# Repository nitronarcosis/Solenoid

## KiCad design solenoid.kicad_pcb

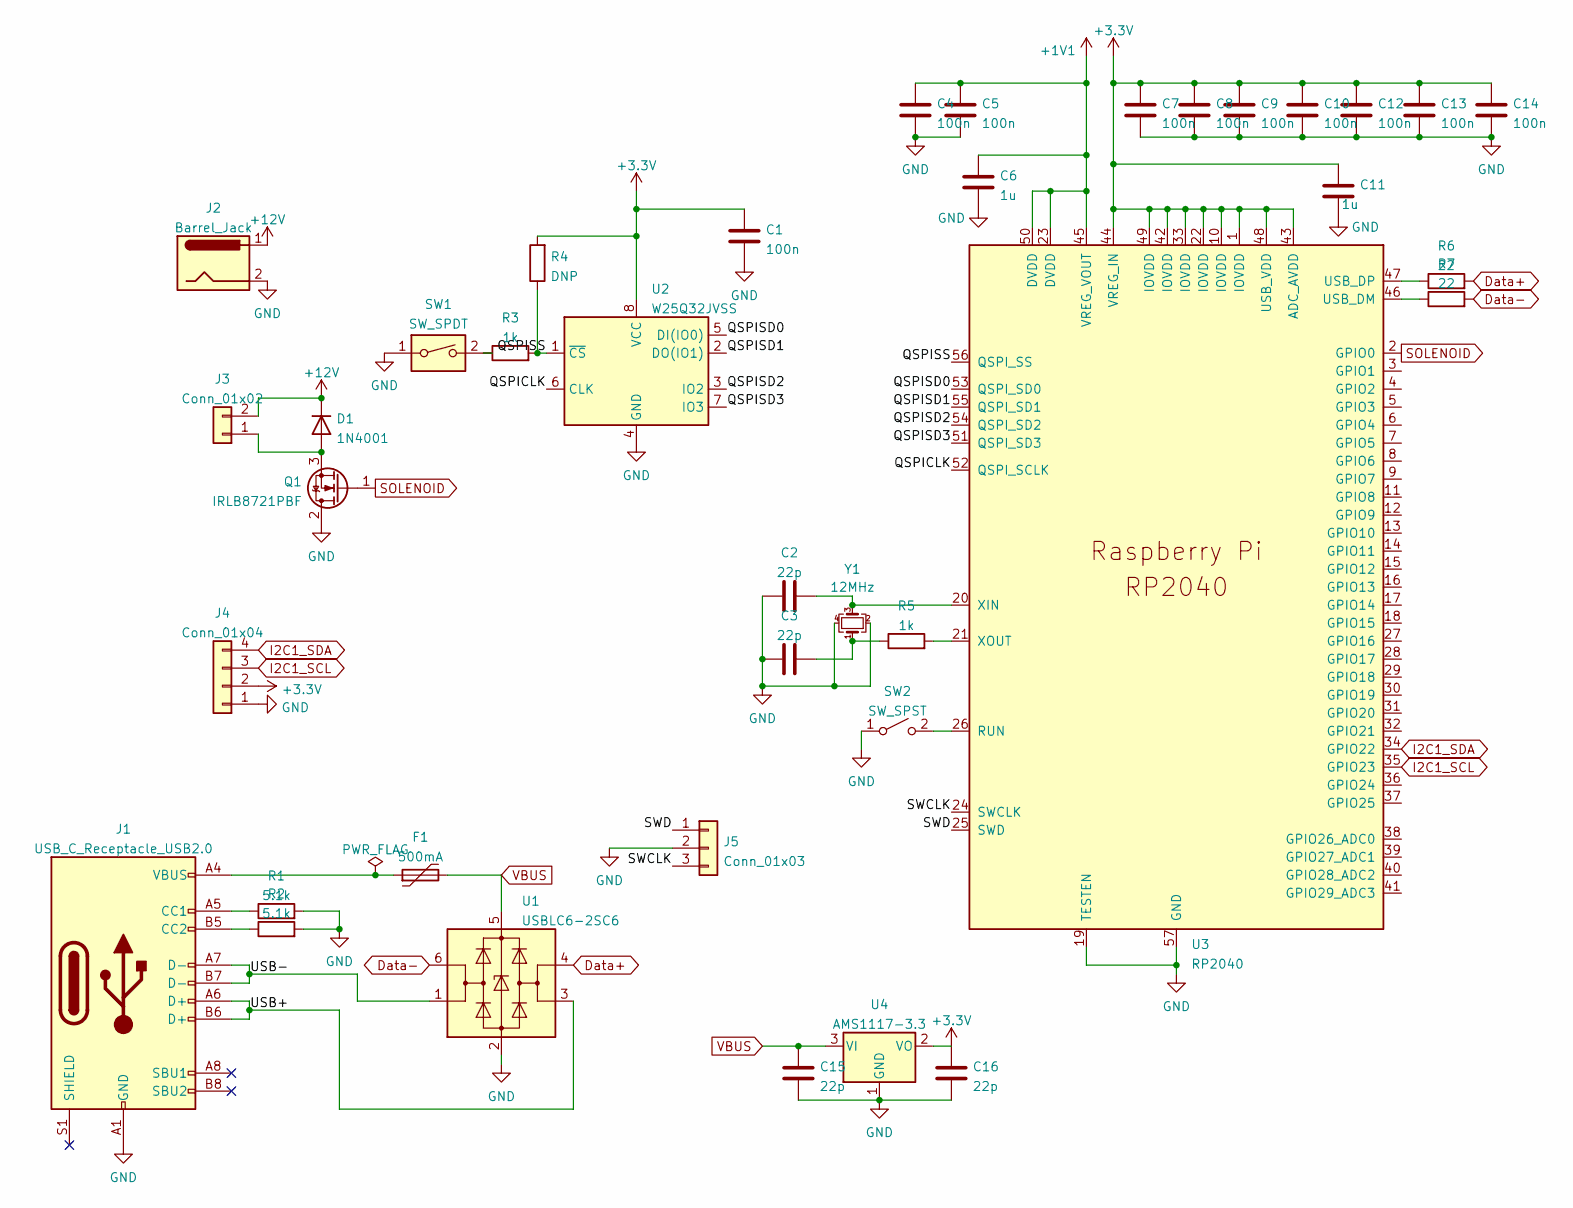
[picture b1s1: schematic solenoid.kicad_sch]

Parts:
C1, C4, C5, C7, C8, C9, C10, C12, C13, C14: 100n; C_0603_1608Metric
C2, C3, C15, C16: 22p; C_0603_1608Metric
C6, C11: 1u; C_0603_1608Metric
D1: 1N4001; D_DO-41_SOD81_P10.16mm_Horizontal
F1: 500mA; Fuse_1206_3216Metric_Pad1.42x1.75mm_HandSolder
J1: USB_C_Receptacle_USB2.0; USB_C_Receptacle_HRO_TYPE-C-31-M-12
J2: Barrel_Jack; BarrelJack_CUI_PJ-063AH_Horizontal
J3: Conn_01x02; PinHeader_1x02_P2.54mm_Vertical
J4: Conn_01x04; PinHeader_1x04_P2.54mm_Vertical
J5: Conn_01x03; PinHeader_1x03_P2.54mm_Vertical
Q1: IRLB8721PBF; TO-220-3_Vertical
R1, R2: 5.1k; R_0603_1608Metric
R3, R5: 1k; R_0603_1608Metric
R4: DNP; R_0603_1608Metric
R6, R7: 22; R_0603_1608Metric
SW1: SW_SPDT; SW_DIP_SPSTx01_Slide_Omron_A6S-110x_W8.9mm_P2.54mm
SW2: SW_SPST; SW_SPST_EVQP0
U1: USBLC6-2SC6; SOT-23-6
U2: W25Q32JVSS; SOIC-8_5.23x5.23mm_P1.27mm
U3: RP2040; RP2040-QFN-56
U4: AMS1117-3.3; SOT-223-3_TabPin2
Y1: 12MHz; Crystal_SMD_3225-4Pin_3.2x2.5mm

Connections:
+1V1: C4.1, C5.1, C6.1, U3.23 (DVDD), U3.45 (VREG_VOUT), U3.50 (DVDD)
+3V3: C1.1, C7.1, C8.1, C9.1, C10.1, C11.1, C12.1, C13.1, C14.1, C16.2, J4.2, R4.2, U2.8 (VCC), U3.1 (IOVDD), U3.10 (IOVDD), U3.22 (IOVDD), U3.33 (IOVDD), U3.42 (IOVDD), U3.43 (ADC_AVDD), U3.44 (VREG_IN), U3.48 (USB_VDD), U3.49 (IOVDD), U4.2 (VO)
+12V: D1.1 (K), J2.1, J3.2
/QSPICLK: U2.6 (CLK), U3.52 (QSPI_SCLK)
/QSPISD0: U2.5 (DI(IO0)), U3.53 (QSPI_SD0)
/QSPISD1: U2.2 (DO(IO1)), U3.55 (QSPI_SD1)
/QSPISD2: U2.3 (IO2), U3.54 (QSPI_SD2)
/QSPISD3: U2.7 (IO3), U3.51 (QSPI_SD3)
/QSPISS: R3.2, R4.1, U2.1 (~CS), U3.56 (QSPI_SS)
/SWCLK: J5.3, U3.24 (SWCLK)
/SWD: J5.1, U3.25 (SWD)
/USB+: J1.A6 (D+), J1.B6 (D+), U1.3 (I/O2)
/USB-: J1.A7 (D-), J1.B7 (D-), U1.1 (I/O1)
Data+: R6.2, U1.4 (I/O2)
Data-: R7.2, U1.6 (I/O1)
GND: C1.2, C2.1, C3.1, C4.2, C5.2, C6.2, C7.2, C8.2, C9.2, C10.2, C11.2, C12.2, C13.2, C14.2, C15.1, C16.1, J1.A1 (GND), J1.A12 (GND), J1.B1 (GND), J1.B12 (GND), J2.2, J4.1, J5.2, Q1.2 (D), R1.2, R2.2, SW1.1, SW2.1 (A), U1.2 (GND), U2.4 (GND), U3.19 (TESTEN), U3.57 (GND), U4.1 (GND), Y1.2, Y1.4
I2C1_SCL: J4.3, U3.35 (GPIO23)
I2C1_SDA: J4.4, U3.34 (GPIO22)
unnamed: C2.2, U3.20 (XIN), Y1.3
unnamed: C3.2, R5.1, Y1.1
unnamed: D1.2 (A), J3.1, Q1.3 (S)
unnamed: F1.1, J1.A4 (VBUS), J1.A9 (VBUS), J1.B4 (VBUS), J1.B9 (VBUS)
unnamed: J1.A5 (CC1), R1.1
unnamed: J1.B5 (CC2), R2.1
unnamed: R3.1, SW1.2
unnamed: R5.2, U3.21 (XOUT)
unnamed: R6.1, U3.47 (USB_DP)
unnamed: R7.1, U3.46 (USB_DM)
unnamed: SW2.2 (B), U3.26 (RUN)
SOLENOID: Q1.1 (G), U3.2 (GPIO0)
VBUS: C15.2, F1.2, U1.5 (VBUS), U4.3 (VI)

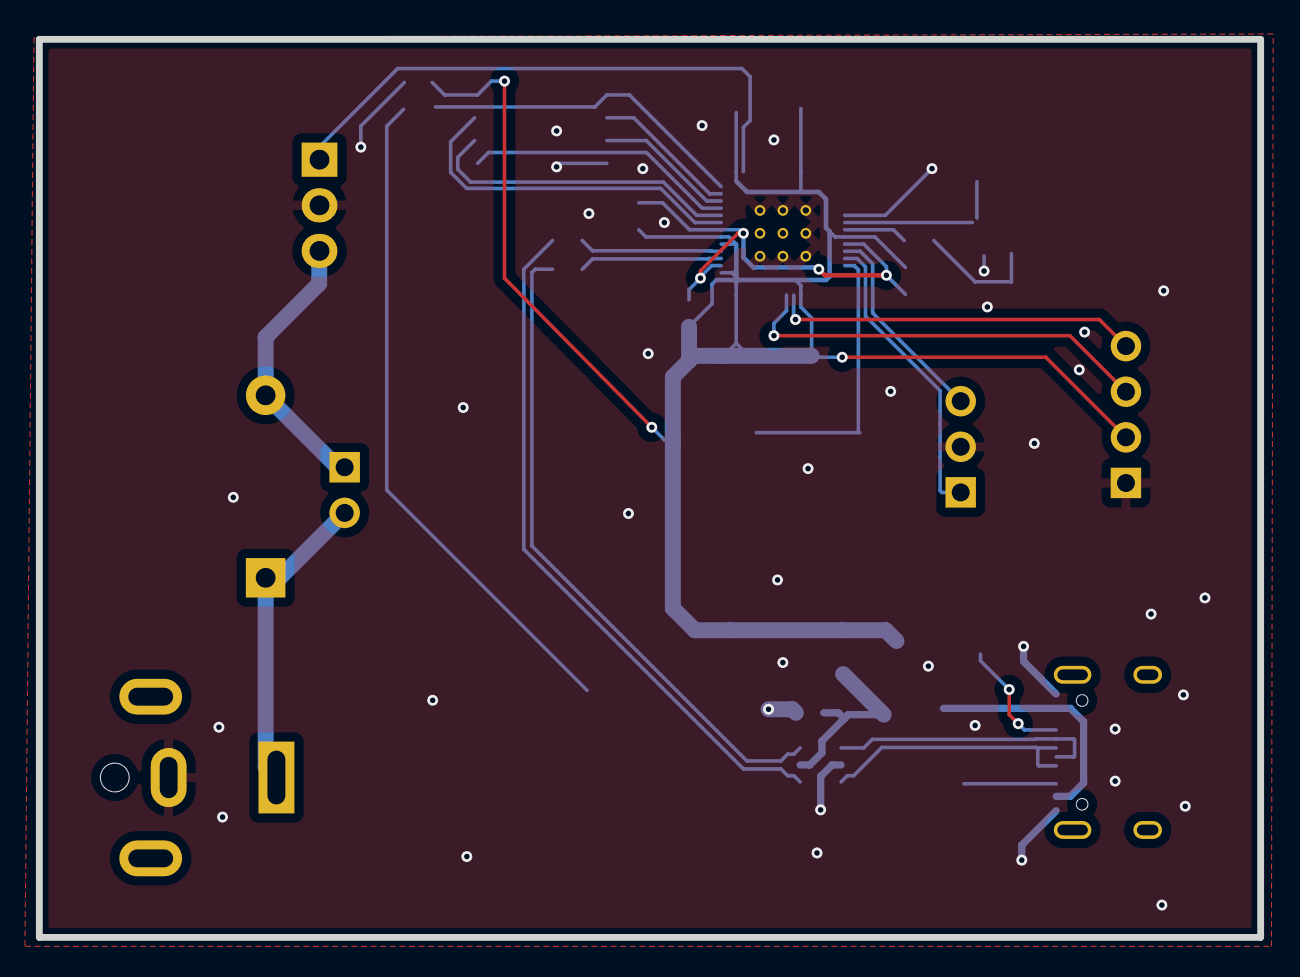
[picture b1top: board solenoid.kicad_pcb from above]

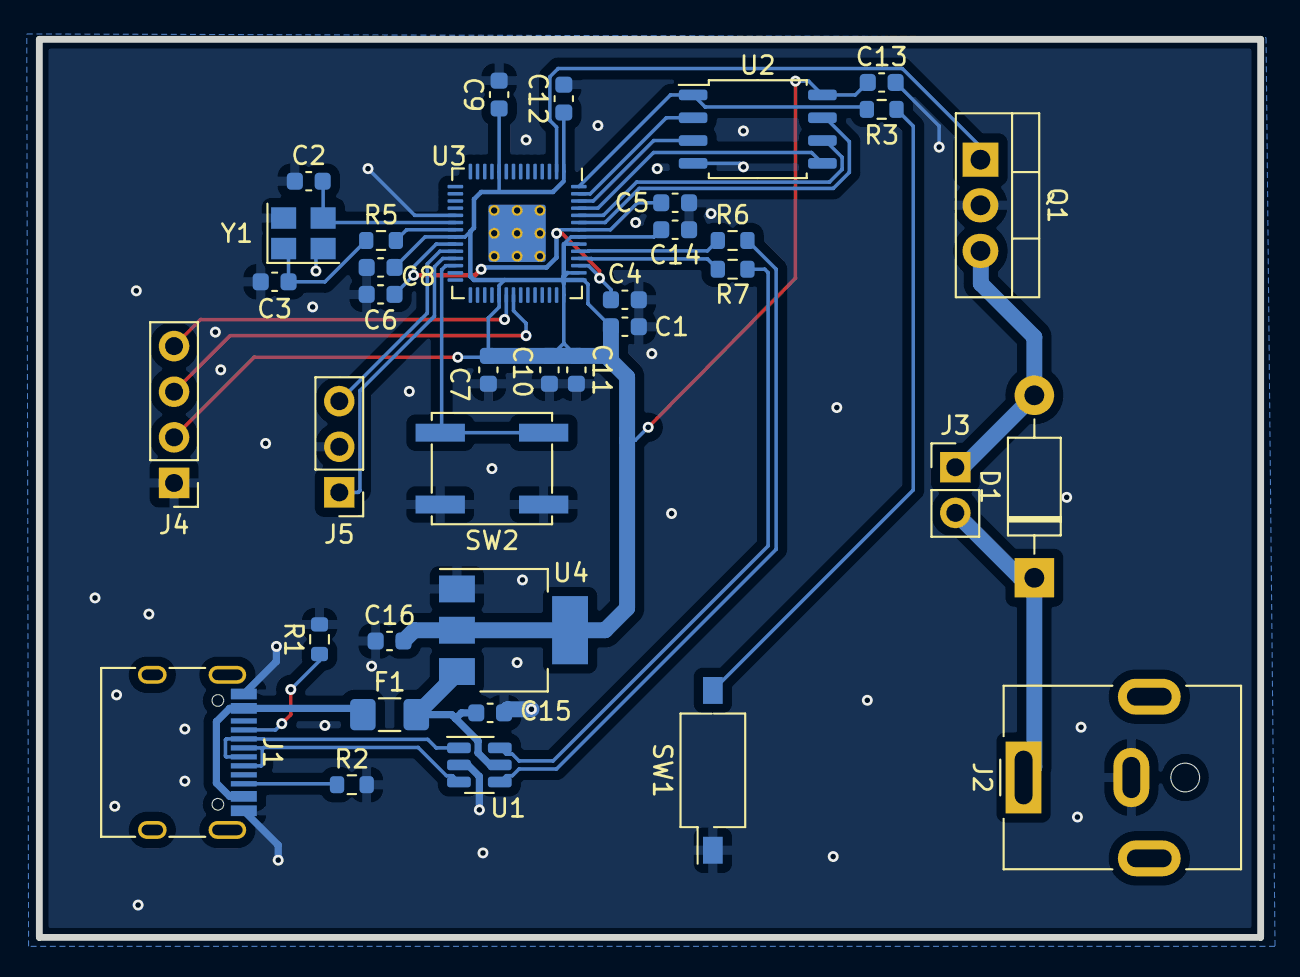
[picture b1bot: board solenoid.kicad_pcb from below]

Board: 2 copper layers, 68.0 x 50.0 mm, 37 parts (37 on the bottom side), 31 nets.

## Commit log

2022-07-17 Fixing borked initial commit.
